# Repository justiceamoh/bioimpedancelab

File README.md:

bioimpedancelab
===============

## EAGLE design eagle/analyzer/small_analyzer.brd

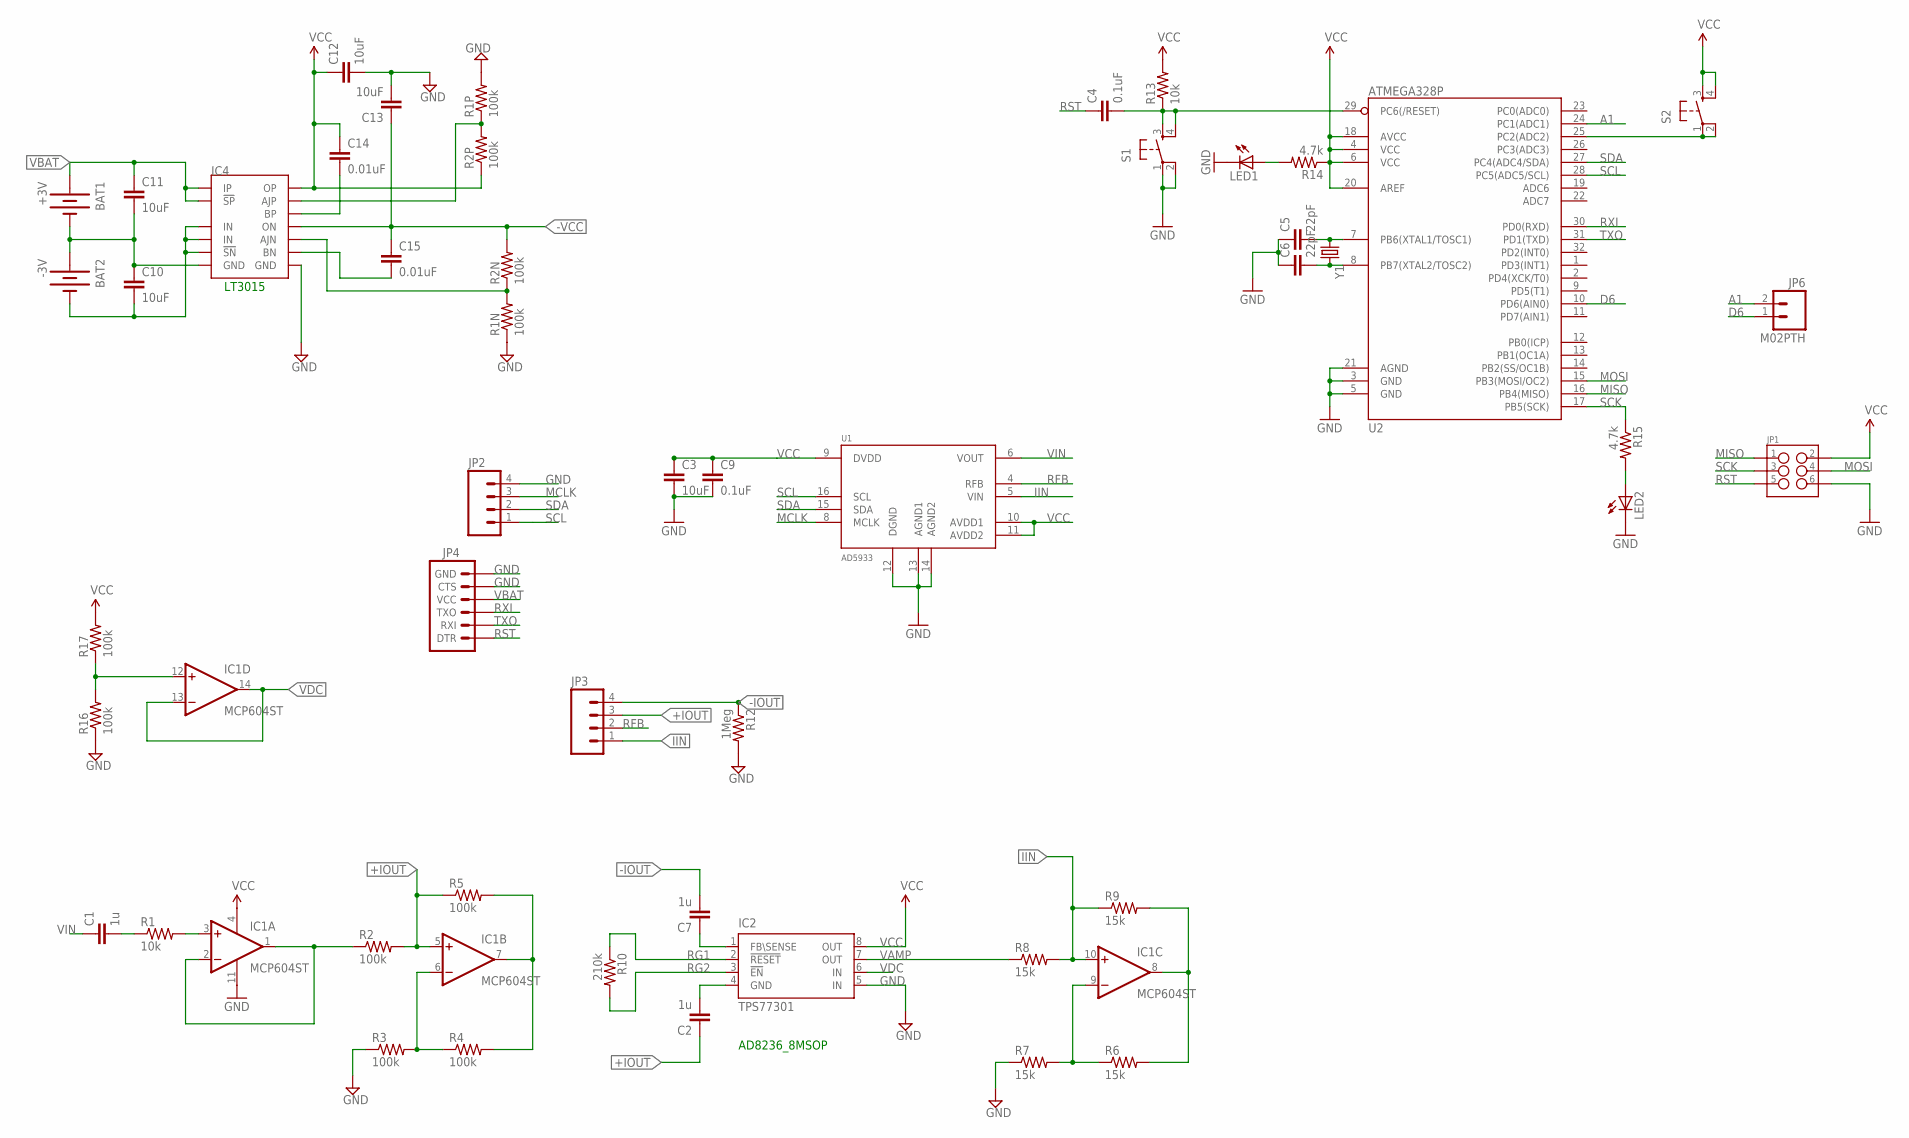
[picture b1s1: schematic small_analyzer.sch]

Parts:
BAT1: +3V; BATTCON_12MM
BAT2: -3V; BATTCON_12MM
C1, C2, C7: 1u; 0603-CAP
C3, C10, C11, C12, C13: 10uF; 0603-CAP
C4: 0.1uF; 0805
C5, C6: 22pF; 0805
C9: 0.1uF; 0603-CAP
C14, C15: 0.01uF; 0603-CAP
IC1: MCP604ST; TSSOP14
IC2: TPS77301; SOP-08
IC4: LT3032; DFN14-4X3DE
JP1: M03X2NO_SILK; 2X3-NS
JP2, JP3: M04PTH; 1X04
JP4: ARDUINO_SERIAL_PROGRAMLOCK; 1X06_LOCK
JP6: M02PTH; 1X02
LED1, LED2: LED0603; LED-0603
R1: 10k; 0603-RES
R1N, R1P, R2N, R2P, R16, R17: 100k; 0805
R2, R3, R4, R5: 100k; 0603-RES
R6, R7, R8, R9: 15k; 0603-RES
R10: 210k; 0603-RES
R12: 1Meg; 0603-RES
R13: 10k; 0805
R14, R15: 4.7k; 0805
S1, S2: TAC_SWITCHSMD; TACTILE_SWITCH_SMD
U1: AD5933; SSOP16
U2: ATMEGA328P; TQFP32-08
Y1: CRYSTAL5X3; CRYSTAL-SMD-5X3

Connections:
+IOUT: C2.1, IC1.5 (+IN), JP3.3, R2.2, R5.1
-IOUT: C7.2, JP3.4, R12.1
-VCC: C13.1, C15.1, IC4.7 (ON), R2N.2
A1: JP6.2, U2.24 (PC1(ADC1))
D6: JP6.1, U2.10 (PD6(AIN0))
GND: C3.2, C5.1, C6.1, C9.2, C12.2, C13.2, IC1.11 (V-), IC2.5 (IN), IC4.5 (GND), JP1.6, JP2.4, JP4.5 (CTS), JP4.6 (GND), LED1.C, LED2.C, R1N.1, R1P.2, R3.1, R7.1, R12.2, R16.1, S1.1, S1.2, U1.12 (DGND), U1.13 (AGND1), U1.14 (AGND2), U2.3 (GND), U2.5 (GND), U2.21 (AGND)
IIN: IC1.10 (+IN), JP3.1, R8.2, R9.1, U1.5 (VIN)
MCLK: JP2.3, U1.8 (MCLK)
MISO: JP1.1, U2.16 (PB4(MISO))
MOSI: JP1.4, U2.15 (PB3(MOSI/OC2))
unnamed: C1.2, R1.1
unnamed: IC1.3 (+IN), R1.2
unnamed: IC1.1 (OUT), IC1.2 (-IN), R2.1
unnamed: C5.2, U2.7 (PB6(XTAL1/TOSC1)), Y1.1
unnamed: IC1.6 (-IN), R3.2, R4.1
unnamed: IC1.7 (OUT), R4.2, R5.2
unnamed: IC1.8 (OUT), R6.2, R9.2
unnamed: IC1.9 (-IN), R6.1, R7.2
unnamed: C6.2, U2.8 (PB7(XTAL2/TOSC2)), Y1.3 (2)
unnamed: LED2.A, R15.2
unnamed: C4.2, R13.1, S1.3, S1.4, U2.29 (PC6(/RESET))
unnamed: LED1.A, R14.2
unnamed: BAT1.GND (-), BAT2.PWR@1 (+), C10.1, C11.2, IC4.4 (GND)
unnamed: IC1.12 (+IN), R16.2, R17.1
unnamed: S2.1, S2.2, U2.25 (PC2(ADC2))
unnamed: BAT2.GND (-), C10.2, IC4.6 (IN), IC4.9 (IN), IC4.10 (!SN)
unnamed: C14.2, IC4.3 (BP)
unnamed: C15.2, IC4.11 (BN)
unnamed: IC4.8 (AJN), R1N.2, R2N.1
unnamed: IC4.2 (AJP), R1P.1, R2P.2
unnamed: C7.1, IC2.1 (FB\SENSE)
unnamed: C2.2, IC2.4 (GND)
RFB: JP3.2, U1.4 (RFB)
RG1: IC2.2 (!RESET), R10.1
RG2: IC2.3 (!EN), R10.2
RST: C4.1, JP1.5, JP4.1 (DTR)
RXI: JP4.3 (TXO), U2.30 (PD0(RXD))
SCK: JP1.3, R15.1, U2.17 (PB5(SCK))
SCL: JP2.1, U1.16 (SCL), U2.28 (PC5(ADC5/SCL))
SDA: JP2.2, U1.15 (SDA), U2.27 (PC4(ADC4/SDA))
TXO: JP4.2 (RXI), U2.31 (PD1(TXD))
VAMP: IC2.7 (OUT), R8.1
VBAT: BAT1.PWR@1 (+), C11.1, IC4.12 (!SP), IC4.14 (IP), JP4.4 (VCC)
VCC: C3.1, C9.1, C12.1, C14.1, IC1.4 (V+), IC2.8 (OUT), IC4.1 (OP), JP1.2, R2P.1, R13.2, R14.1, R17.2, S2.3, S2.4, U1.9 (DVDD), U1.10 (AVDD1), U1.11 (AVDD2), U2.4 (VCC), U2.6 (VCC), U2.18 (AVCC), U2.20 (AREF)
VDC: IC1.13 (-IN), IC1.14 (OUT), IC2.6 (IN)
VIN: C1.1, U1.6 (VOUT)

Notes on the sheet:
AD8236_8MSOP
LT3015

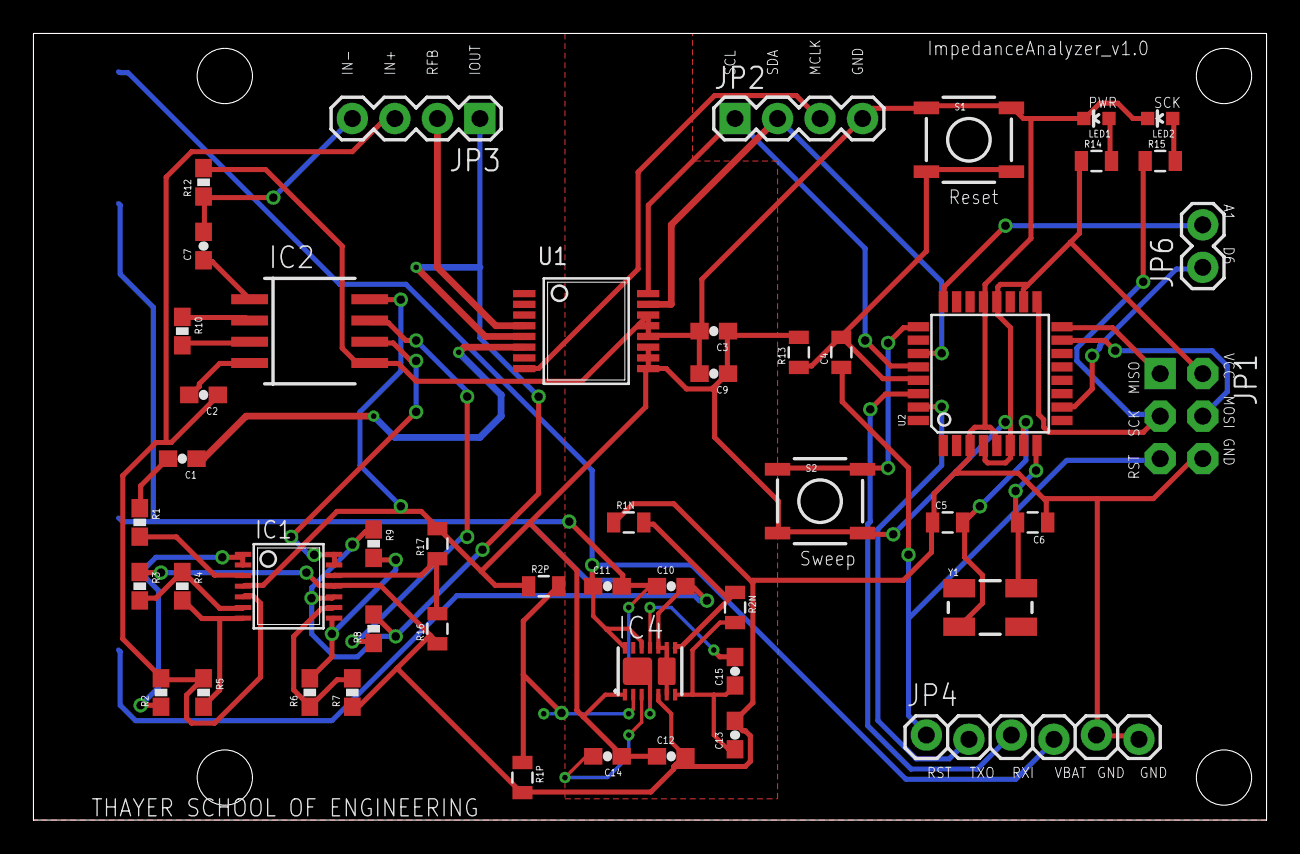
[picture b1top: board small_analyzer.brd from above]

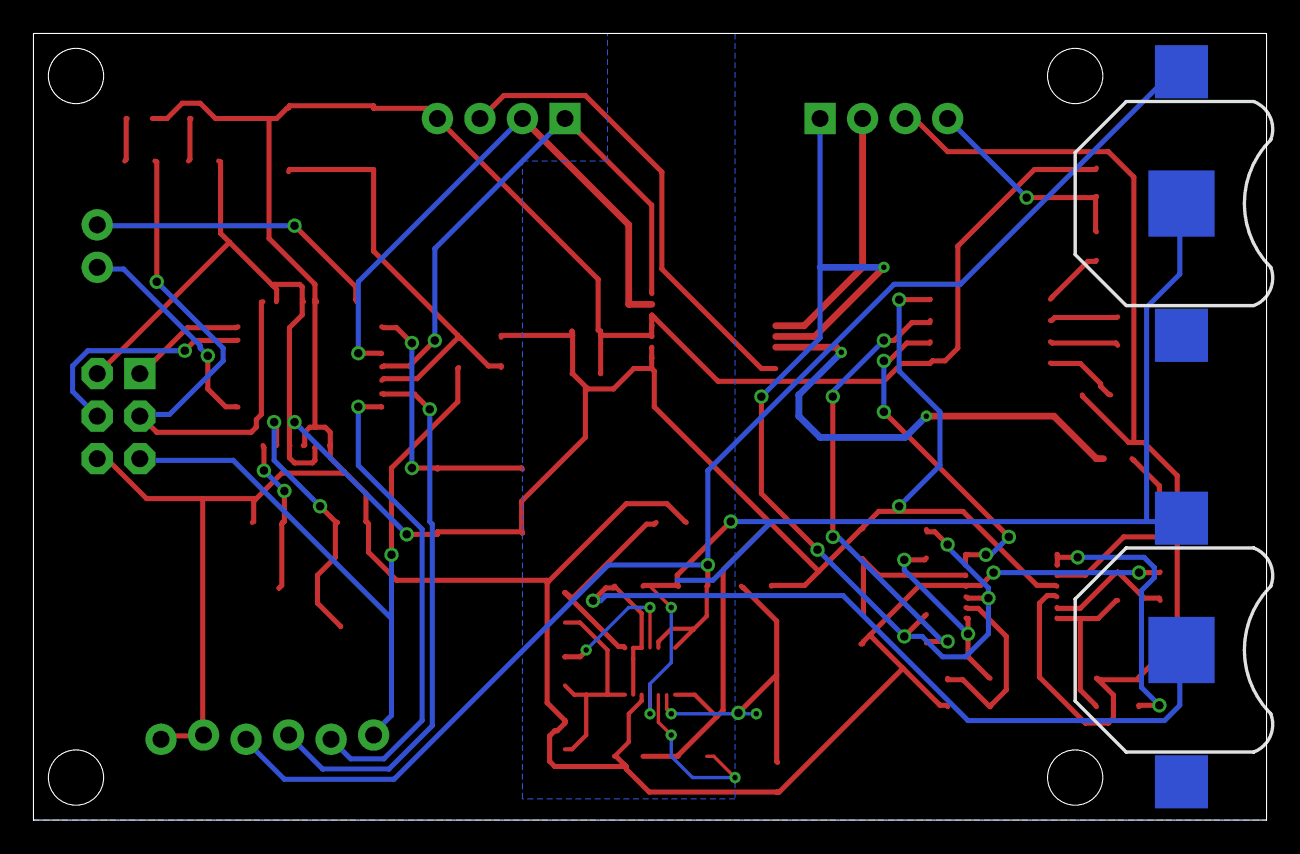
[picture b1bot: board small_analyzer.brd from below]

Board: 2 copper layers, 73.7 x 47.0 mm, 55 parts (2 on the bottom side), 46 nets.

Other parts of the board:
U$1, U$2, U$3, U$4: STAND-OFF

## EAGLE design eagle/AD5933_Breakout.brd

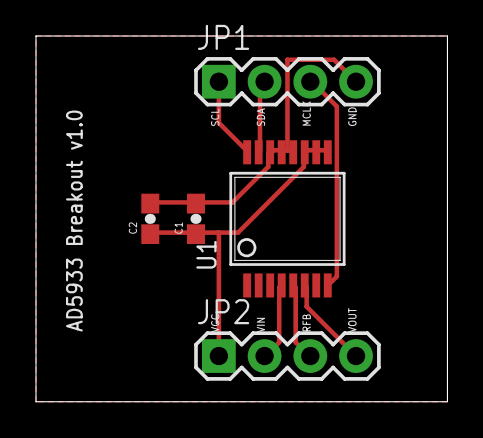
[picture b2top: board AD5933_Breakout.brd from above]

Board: 2 copper layers, 22.9 x 20.3 mm, 5 parts (0 on the bottom side), 8 nets.

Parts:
C1: 0.1uF; 0603-CAP
C2: 10uF; 0603-CAP
JP1, JP2: 1X04
U1: AD5933; SSOP16

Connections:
GND: C1.2, C2.2, JP1.4, U1.12, U1.13, U1.14
MCLK: JP1.3, U1.8
RFB: JP2.2, U1.4
SCL: JP1.1, U1.16
SDA: JP1.2, U1.15
VCC: C1.1, C2.1, JP2.1, U1.9, U1.10, U1.11
VIN: JP2.3, U1.5
VOUT: JP2.4, U1.6

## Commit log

2013-10-09 initialized bioimpedance repo
2013-10-09 moved repo to thayer servers
2013-10-09 first iteration of board
2013-10-09 both board and schematic looking good
2013-10-09 first pcb routing
2013-10-09 rerouted board
2013-10-09 discovered downloaded ad5933 footprint is buggy
2013-10-10 clean up
2013-10-16 switched headers and rerouted all pins
2013-10-16 fixed rules and cleared clearance errors
2013-10-16 augmented size to fit on breadboard
2013-10-16 added gerber files
2013-10-23 added top and bottom copper pours to pcb
2013-10-25 created new gerber files
2013-10-25 cleanup
2013-10-25 pcb ordered
2013-10-28 added pcb order
2013-11-12 cleaned up temp.c and fixed minor bugs
2013-11-13 cleaned up arduino code to enable compile
2013-11-13 bug fixes
2013-11-20 removed dependence on button press
2013-11-21 successfully reading temperature
2013-11-24 added journal_club paper
2013-11-24 cleaned up project directory, added new ino project
2013-11-24 added journal club papers
2013-11-24 rewrote runsweep function
2013-11-24 successfully running sweep
2013-11-24 changed operation range to 1, PGA gain 1
2013-12-02 fixed interchanged RFB and VIN labels on board
2013-12-02 modified sketch for easy input of frequency sweep parameters
2013-12-02 computed for impedance and frequency per sweep
2013-12-04 editted sketch for serial com with matlab
2013-12-05 fixed temperature reading bug
2013-12-05 testing frequency sweep
2013-12-11 started works on impedance gui
2013-12-11 editted sketch to format data transmission in accordance with matlab listener, usb_listener.m
2013-12-11 usb listener working correctly
2013-12-11 clean up, usb_listener receiving and plotting impedance and phase values
2013-12-11 finished matlab GUI
2013-12-11 further works on gui
2013-12-14 fixed bug that prevented subsequent sweeps
2013-12-15 cleaning workspace
2014-01-27 added simetrix files
2014-01-28 troubleshoting arduino sketch, attempting to use ARM maple board, adding journal club papers
2014-02-03 added analyzer layout
2014-02-03 added tetra_polar schematics
2014-02-03 added analyzer ic with mcu
2014-02-10 added ground planes, expanded board, changed mcu to atmega328
2014-02-17 cleaned local repo
2014-02-17 all pins successfully routed
2014-02-23 updated howland circuit to right configuration for our purposes
2014-02-24 fixed drc laws
2014-02-24 local updates
2014-02-24 added sweep push button and decoupling caps
2014-02-27 updates to circuit
2014-02-27 added fast opamp datasheet and changes to howland circuit
2014-03-20 updates to howland circuits
2014-03-20 added dual voltage regulator to board
2014-03-20 updated schematic to dual voltage regulator, errors in board
2014-03-24 analyzer version 1 as submitted for pcb fab
2014-05-01 fixed calibration bug
2014-05-01 very well calibrated
2014-05-01 added maple stuff
2014-05-08 started updating FSM for additional functionality
2014-05-10 cleaned up and added python code for ic control

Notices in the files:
parts and their libraries:
SparkFun-Capacitors: Licensing: CC v3.0 Share-Alike You are welcome to use this library for commercial purposes.
